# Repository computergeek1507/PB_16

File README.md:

# Copyright and Disclaimer
Copyright: Scott Hanson

This documentation describes Open Hardware and is licensed under the CERN Open Hardware License Version 2 - Strongly Reciprocal. (CERN-OHL-S)

You may redistribute and modify this documentation under the terms of the CERN OHL-S-v2 (https://ohwr.org/cern_ohl_s_v2.txt). This documentation is distributed WITHOUT ANY EXPRESS OR IMPLIED WARRANTY, INCLUDING OF MERCHANTABILITY, SATISFACTORY QUALITY AND FITNESS FOR A PARTICULAR PURPOSE. Please see the CERN OHL v2-S for applicable conditions

**Under CERN OHL-S-v2, derivative work must be publicly released as defined in subsection 3.3**

# BBB/PB 'Family' of Controllers

The PB16/BBB16 Pixel Controllers are designed as open source DIY hobbyist controllers. 
They all run FPP to drives the ports and serial ports. 
They are designed to be modular and support many use cases. It runs a full Linux operating system with ethernet, WIFI and audio supported over the USB port. It can run in standalone, or be used with other controllers/devices. All the design files are open source and available on github. Open source applications were used to create the controllers. [KiCad](http://kicad.org/) was used for the PCB design, and [LibreOffice](https://www.libreoffice.org/) for the documentation.

# [PB 16v1](PB_16v1/README.md)
The "Original" Pocketbeagle Version with 16 pixel ports, 2 serial ports and an expansion header for additional 16 pixel outputs.
The design was made with all through hole components for easy assembly by most users.

# [PB 16v2](PB_16v2_SMD/README.md)
The PB 16v2 is a Surface Mount(SMD) Pocketbeagle Version with 16 pixel ports, 1 remote differential port, 2 serial ports, and an expansion header for additional 16 pixel outputs. The v2 has an improved reverse protect circuit and USB power supply circuit.

# [BBB 16v2](BBB_16/README.md)
The BBB 16v2 is a BeagleBone Version with 16 pixel ports, 1 remote differential port, 2 serial ports, and an expansion header for additional 16 pixel outputs. Uses Falcon v4 (24 pin) Expansion Pinout.

# [BBB 16v2 SMD](BBB_16_SMD/README.md) 
The BBB 16v2 SMD is a Surface Mount(SMD) BeagleBone Version with 16 pixel ports, 1 remote differential port, 2 serial ports, and an expansion header for additional 16 pixel outputs. Uses Falcon v4 (24 pin) Expansion Pinout.

### Common Features of the PB 16v1, PB 16v2, & BBB 16v2
* Powered by FPP Falcon Player
* Standalone/Master/Remote/Bridge Support
* 16 3-Wire Pixel Ports
* 700 pixel per output at 40 FPS or 1300 at 20 FPS
* 2 DMX Serial Outputs
* Fused Powered DMX Output
* USB port for Ethernet,WIFI, or Audio
* OLED Display header
* Adafruit Real Time Clock Header Connector
* 2 pin GPIO Header for Push Button or Relay Support
* 5v - 24v Vin Support
* Expansion Header for additional 16 pixel outputs, Supports Falcon v3 (40 pin) Expansion Boards.

### Features of the PB 16v1
* Through Hole Assemply
* 1 RJ-45 Connector with DMX/Renard Wiring Support.
* 1 RJ-45 Connector with DMX/LOR Wiring Support.
* Only Supports DMX Protocol over Serial Ports.

### Features of the PB 16v2 & BBB 16v2
* 1 RJ-45 Connector for a remote differential port.
* 1 RJ-45 Connector with DMX/LOR Wiring Support.
* Supports DMX/Renard/Lor Protocol over Serial Ports.

## [Ordering Instructions](https://github.com/computergeek1507/PB_16/blob/master/JLC_PCB.md)
## [Flashing EEPROM Instructions](https://github.com/computergeek1507/PB_16/blob/master/Flashing_EEPROM.md)

## Variants
I created different variants of the PB 16, to fit my specific needs.
* [**PB 16v1**](PB_16v1/README.md) - Original Pocketbeagle Version with 16 pixel ports, 2 serial ports and an expansion header(40 pins) for additional 16 pixel outputs.
* [**PB 16v2**](PB_16v2_SMD/README.md) - **Surface Mount(SMD)** Pocketbeagle Version with 16 pixel ports, 1 remote differential port, 2 serial ports, and an expansion header(40 pins) for additional 16 pixel outputs.
* [**BBB 16v2**](BBB_16/README.md) - Beaglebone Version with 16 pixel ports, 1 remote differential port, 2 serial ports and an expansion header for additional 16 pixel outputs. Uses Falcon v4 Expansion Pinout(24 pins).
* [**BBB 16v2 SMD**](BBB_16_SMD/README.md) - **Surface Mount(SMD)** Beaglebone Version with 16 pixel ports, 1 remote differential port, 2 serial ports and an expansion header for additional 16 pixel outputs. Uses Falcon v4 Expansion Pinout(24 pins).
* [**BBB 16 Flex**](BBB_16_Flex/README.md) - BBB 16 PCB to use with the HolidayCoro Flex System. This is a **Surface Mount(SMD)** Design.
* [**BBB 16 Expansion**](BBB_16_Expansion/README.md) - BBB 16v2 PCB with Three Expansion Board Ports for 48 outputs. Uses Falcon v4 Expansion Pinout. This is a **Surface Mount(SMD)** Design.
* [**PB 16 Expansion**](PB_16_Expansion/README.md) - Small Form Factor PB 16 with Two Expansion Board Ports(40 pins) for 32 outputs.
* [**PB 16 Mini**](PB_16_Mini/README.md) - Small Form Factor PB 16 with one Expansion Board Port(40 pins) for 16 ouputs and two Serial Outputs.
* [**PB 16 Flex**](PB_16_Flex/README.md) - PB 16 PCB to use with the HolidayCoro Flex System.
<!--- * [**PB 16 E682**](PB_16_E682/README.md) - Adapter PCB to use a Pocketbeagle with a Sandevice E682. (This is a proof of concept, not designed for extended use)-->
* [**PB 16 E682 Serial**](PB_16_E682_Serial/README.md) - Serial Output PCB to for PB 16 E682 or PB 16 Expansion.

## Addon Boards

The PB16 Controller contains an expansion header. The expansion header can drive 16 additional pixel ports. I have also created addition addon boards to work with the expansion port. These Expansions will work with Kulp Controllers, but **not** Falcon Controllers.

* [**16 Expansion**](16_Expansion/README.md) - 16 Port Local Expansion. Supports PB 16 (40 pins) Connectors.
* [**16 Expansion 24pin**](16_Expansion_24pin/README.md) - 16 Port Local Expansion. Supports BBB 16v2 (24 pins) Connectors.
* [**16 Expansion SMD**](16_Expansion_SMD/README.md) - 16 Port Local Expansion. Supports PB 16 (40 pins) Connectors. This is a **Surface Mount(SMD)** Design.
* [**16 Expansion SMD 24pin**](16_Expansion_SMD_24pin/README.md) - 16 Port Local Expansion. Supports BBB 16v2 (24 pins) Connectors. This is a **Surface Mount(SMD)** Design.
* [**Diff Expansion**](Diff_Expansion/README.md) - 4 Port Remote Differential Expansion. Supports PB 16 (40 pins) & BBB 16 (24 pins) Connectors.
* [**Multi Expansion**](Multi_Expansion/README.md) - 8 Port Local & 2 Port Remote Differential Expansion. **Only Supports PB 16 (40 pins) Connectors.**
* [**Quad Diff Out**](Quad_Diff_Out/README.md) - 1 Port Remote Differential Expansion.
* [**Four Out**](Four_Out/README.md) - 4 Port Local Expansion. Supports PB 16 (40 pins) & BBB 16 (24 pins) Connectors.
* [**Receiver Out**](Receiver_Out/README.md) - 4 Port Remote Receiver Board for use with Remote Differential Expansions.
* [**Receiver Out SMD**](Receiver_Out_SMD/README.md) - 4 Port Remote Receiver Board for use with Remote Differential Expansions. This is a **Surface Mount(SMD)** Design.

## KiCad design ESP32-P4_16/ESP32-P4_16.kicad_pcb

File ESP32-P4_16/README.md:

# Copyright and Disclaimer
Copyright: Scott Hanson

This documentation describes Open Hardware and is licensed under the CERN Open Hardware License Version 2 - Strongly Reciprocal. (CERN-OHL-S)

You may redistribute and modify this documentation under the terms of the CERN OHL-S-v2 (https://ohwr.org/cern_ohl_s_v2.txt). This documentation is distributed WITHOUT ANY EXPRESS OR IMPLIED WARRANTY, INCLUDING OF MERCHANTABILITY, SATISFACTORY QUALITY AND FITNESS FOR A PARTICULAR PURPOSE. Please see the CERN OHL v2-S for applicable conditions

**Under CERN OHL-S-v2, derivative work must be publicly released as defined in subsection 3.3**

# ESP32-P4 16

**WIP, Do not use**

The ESP32-P4 16 is a ESP32-P4 based 16 port controller. All the design files are open source and available on github.

## [Interactive BOM](https://computergeek1507.github.io/PB_16/ESP32-P4_16/bom/ibom)

## [Part BOM](https://github.com/computergeek1507/PB_16/raw/master/ESP32-P4_16/ESP32-P4_16_BOM.ods)

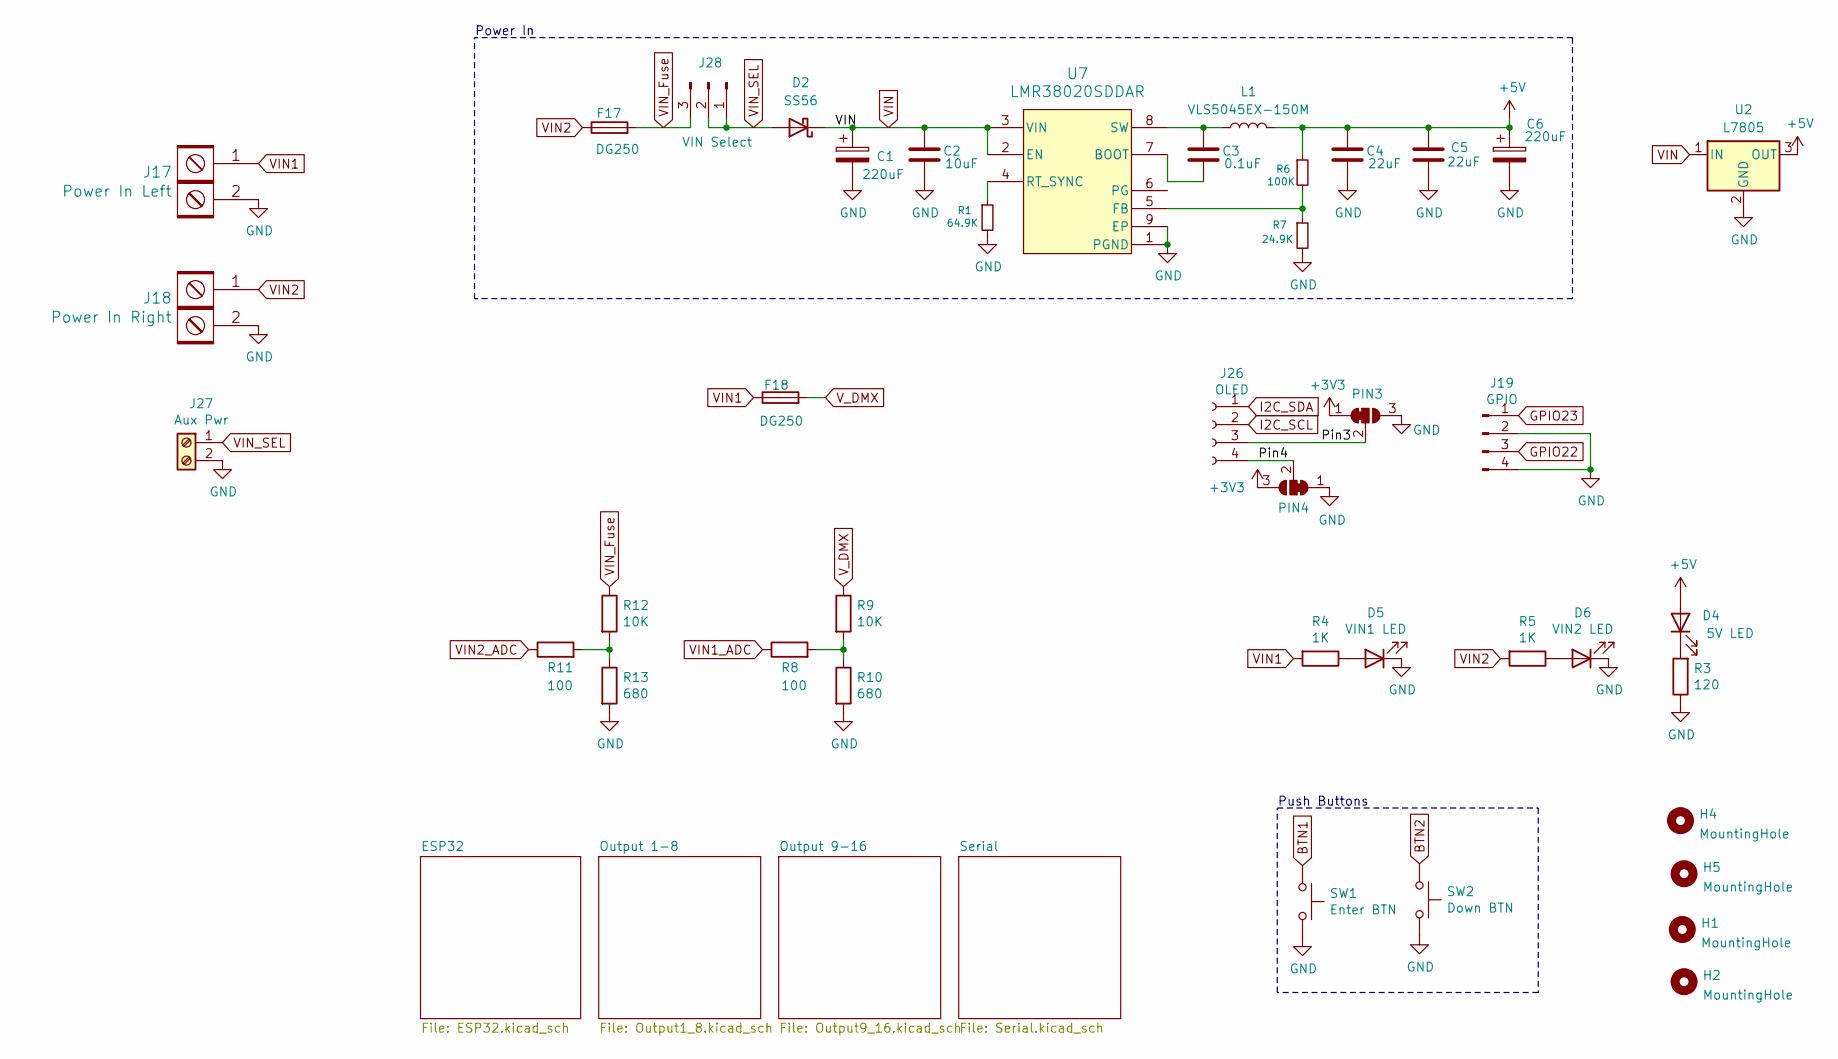
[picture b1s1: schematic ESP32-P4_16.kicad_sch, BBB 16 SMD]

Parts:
C1, C6: 220uF; CP_Elec_8x10.5; LCSC C3340
C2: 10uF; C_1206_3216Metric; LCSC_PN C13585
C3: 0.1uF; C_0603_1608Metric; MPN CC0603KRX7R9BB104; LCSC C14663
C4, C5: 22uF; C_1206_3216Metric; LCSC_PN C1859
D2: SS56; D_SMA; LCSC C65009
D4: 5V LED; LED_0603_1608Metric; MPN LTST-C190KRKT; Digi-Key_PN 160-1436-2-ND
D5: VIN1 LED; LED_0603_1608Metric; MPN LTST-C190KRKT; Digi-Key_PN 160-1436-2-ND
D6: VIN2 LED; LED_0603_1608Metric; MPN LTST-C190KRKT; Digi-Key_PN 160-1436-2-ND
F17: DG250; Fuse_1812_4532Metric; MPN 3544-2
F18: DG250; Fuse_1812_4532Metric
H1, H2, H4, H5: MountingHole; MountingHole_3.7mm
J17: Power In Left; BARRIER_BLOCK_1ROW_2POS_P9.5MM; MPN OSTYK51102030; Digi-Key_PN ED2953-ND
J18: Power In Right; BARRIER_BLOCK_1ROW_2POS_P9.5MM; MPN OSTYK51102030; Digi-Key_PN ED2953-ND
J19: GPIO; JST_XH_B4B-XH-A_1x04_P2.50mm_Vertical; MPN B4B-XH-A(LF)(SN); Digi-Key_PN 455-2249-ND
J26: OLED; OLED-SSD1306-128X64-I2C-THT_2HOLE; MPN PPTC041LFBN-RC; Digi-Key_PN S7002-ND
J27: Aux Pwr; PHOENIX_MKDS1_2-3.81; MPN 1727010; Digi-Key_PN 277-1947-ND
J28: VIN Select; PinHeader_1x03_P2.54mm_Vertical; MPN 61300311121; Digi-Key_PN 732-5316-ND
L1: VLS5045EX-150M; IND_VLS5045EX-150M; MPN VLS5045EX-150M; Digi-Key_PN 445-174845-1-ND
PIN3: Jumper; SolderJumper-3_P1.3mm_Bridged12_Pad1.0x1.5mm
PIN4: JUMPER; SolderJumper-3_P1.3mm_Bridged12_Pad1.0x1.5mm
R1: 64.9K; R_0603_1608Metric; LCSC C14891
R3: 120; R_0603_1608Metric; MPN CRGCQ0603F120R; Digi-Key_PN A129677CT-ND
R4, R5: 1K; R_0603_1608Metric; MPN RC0603FR-071KL; Digi-Key_PN 311-1.00KHRTR-ND
R6: 100K; R_0603_1608Metric; LCSC C25803
R7: 24.9K; R_0603_1608Metric; LCSC C25962
R8, R11: 100; R_0603_1608Metric; MPN RMCF0603FT100R; Digi-Key_PN RMCF0603FT100RCT-ND
R9, R12: 10K; R_0603_1608Metric; MPN RC0603FR-0710KL; Digi-Key_PN 311-10.0KHRCT-ND
R10, R13: 680; R_0603_1608Metric; MPN RC0603FR-07680RL; Digi-Key_PN 311-680HRCT-ND
SW1: Enter BTN; SW_Push_1P1T_NO_6x6mm_H9.5mm; MPN PTS645SL50SMTR92 LFS; Digi-Key_PN CKN9088CT-ND
SW2: Down BTN; SW_Push_1P1T_NO_6x6mm_H9.5mm; MPN PTS645SL50SMTR92 LFS; Digi-Key_PN CKN9088CT-ND
U2: L7805; OKI-78SR_Horz
U7: LMR38020SDDAR; DDA0008E-IPC_A; MPN LMR38020SDDAR; Digi-Key_PN 296-LMR38020SDDARCT-ND

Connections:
+3V3: PIN3.1 (A), PIN4.3 (B); also elsewhere on the board
+5V: C4.1, C5.1, C6.1, D4.2 (A), L1.2, R6.1, U2.3 (OUT); also elsewhere on the board
/Pin3: J26.3, PIN3.2 (C)
/Pin4: J26.4, PIN4.2 (C)
BTN1: SW1.1; also elsewhere on the board
BTN2: SW2.1; also elsewhere on the board
GND: C1.2, C2.2, C4.2, C5.2, C6.2, D5.1 (K), D6.1 (K), J17.2, J18.2, J19.2, J19.4, J27.2, PIN3.3 (B), PIN4.1 (A), R1.2, R3.1, R7.2, R10.2, R13.2, SW1.2, SW2.2, U2.2 (GND), U7.1 (PGND), U7.9 (EP); also elsewhere on the board
GPIO22: J19.3; also elsewhere on the board
GPIO23: J19.1; also elsewhere on the board
I2C_SCL: J26.2; also elsewhere on the board
I2C_SDA: J26.1; also elsewhere on the board
unnamed: D4.1 (K), R3.2
unnamed: D5.2 (A), R4.1
unnamed: D6.2 (A), R5.1
unnamed: R8.2, R9.2, R10.1
unnamed: R11.2, R12.2, R13.1
unnamed: C3.2, U7.7 (BOOT)
unnamed: R6.2, R7.1, U7.5 (FB)
unnamed: R1.1, U7.4 (RT_SYNC)
unnamed: C3.1, L1.1, U7.8 (SW)
VIN: C1.1, C2.1, D2.1 (K), U2.1 (IN), U7.2 (EN), U7.3 (VIN)
VIN1: F18.1, J17.1, R4.2; also elsewhere on the board
VIN1_ADC: R8.1; also elsewhere on the board
VIN2: F17.1, J18.1, R5.2; also elsewhere on the board
VIN2_ADC: R11.1; also elsewhere on the board
VIN_Fuse: F17.2, J28.3, R12.1
VIN_SEL: D2.2 (A), J27.1, J28.1, J28.2
V_DMX: F18.2, R9.1; also elsewhere on the board

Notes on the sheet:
Push Buttons
Power In

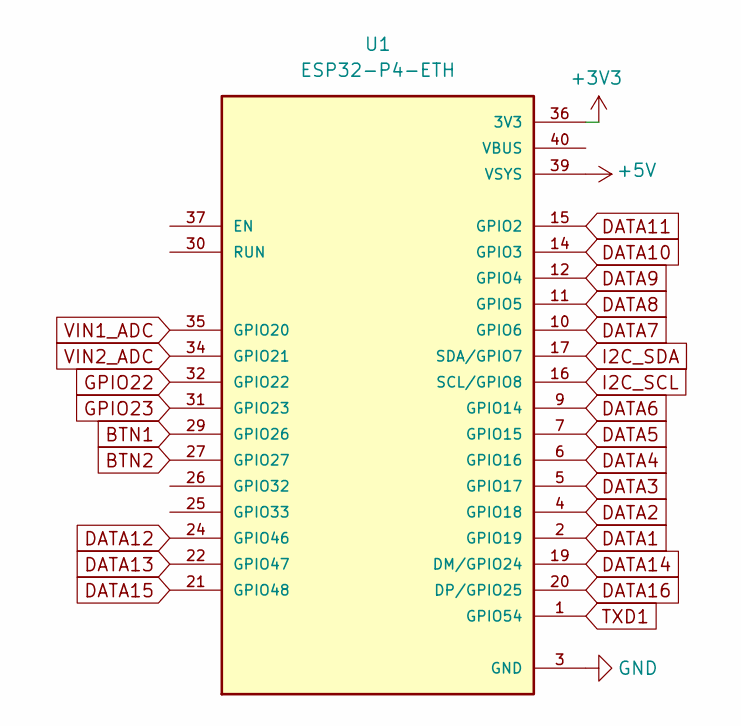
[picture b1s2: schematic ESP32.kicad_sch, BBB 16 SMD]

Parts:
U1: ESP32-P4-ETH; MODULE_ESP32-P4-ETH

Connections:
+3V3: U1.36 (3V3); also elsewhere on the board
+5V: U1.39 (VSYS); also elsewhere on the board
BTN1: U1.29 (GPIO26); also elsewhere on the board
BTN2: U1.27 (GPIO27); also elsewhere on the board
DATA1: U1.2 (GPIO19); also elsewhere on the board
DATA2: U1.4 (GPIO18); also elsewhere on the board
DATA3: U1.5 (GPIO17); also elsewhere on the board
DATA4: U1.6 (GPIO16); also elsewhere on the board
DATA5: U1.7 (GPIO15); also elsewhere on the board
DATA6: U1.9 (GPIO14); also elsewhere on the board
DATA7: U1.10 (GPIO6); also elsewhere on the board
DATA8: U1.11 (GPIO5); also elsewhere on the board
DATA9: U1.12 (GPIO4); also elsewhere on the board
DATA10: U1.14 (GPIO3); also elsewhere on the board
DATA11: U1.15 (GPIO2); also elsewhere on the board
DATA12: U1.24 (GPIO46); also elsewhere on the board
DATA13: U1.22 (GPIO47); also elsewhere on the board
DATA14: U1.19 (DM/GPIO24); also elsewhere on the board
DATA15: U1.21 (GPIO48); also elsewhere on the board
DATA16: U1.20 (DP/GPIO25); also elsewhere on the board
GND: U1.3 (GND), U1.8 (GND), U1.13 (GND), U1.18 (GND), U1.23 (GND), U1.28 (GND), U1.33 (GND), U1.38 (GND); also elsewhere on the board
GPIO22: U1.32 (GPIO22); also elsewhere on the board
GPIO23: U1.31 (GPIO23); also elsewhere on the board
I2C_SCL: U1.16 (SCL/GPIO8); also elsewhere on the board
I2C_SDA: U1.17 (SDA/GPIO7); also elsewhere on the board
TXD1: U1.1 (GPIO54); also elsewhere on the board
VIN1_ADC: U1.35 (GPIO20); also elsewhere on the board
VIN2_ADC: U1.34 (GPIO21); also elsewhere on the board

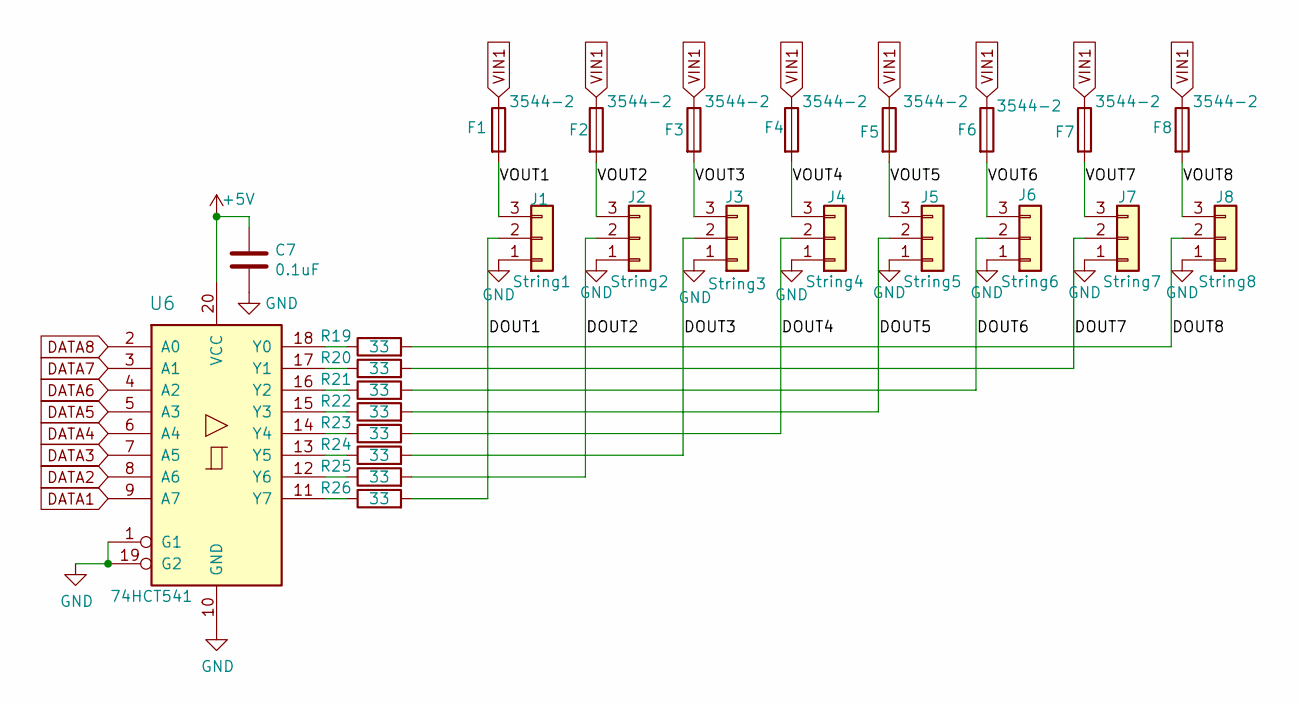
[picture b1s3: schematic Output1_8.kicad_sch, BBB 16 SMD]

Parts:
C7: 0.1uF; C_0603_1608Metric; MPN CL10B104KB8NNWC; Digi-Key_PN 1276-1935-2-ND
F1, F2, F3, F4, F5, F6, F7, F8: 3544-2; Fuse_1812_4532Metric; MPN 3544-2
J1: String1; DG250-3.5-03P; MPN 1843619/OSTTJ0311530
J2: String2; DG250-3.5-03P; MPN 1843619/OSTTJ0311530
J3: String3; DG250-3.5-03P; MPN 1843619/OSTTJ0311530
J4: String4; DG250-3.5-03P; MPN 1843619/OSTTJ0311530
J5: String5; DG250-3.5-03P; MPN 1843619/OSTTJ0311530
J6: String6; DG250-3.5-03P; MPN 1843619/OSTTJ0311530
J7: String7; DG250-3.5-03P; MPN 1843619/OSTTJ0311530
J8: String8; DG250-3.5-03P; MPN 1843619/OSTTJ0311530
R19, R20, R21, R22, R23, R24, R25, R26: 33; R_0603_1608Metric; MPN CN34J330CT; LCSC C23140
U6: 74HCT541; TSSOP-20_4.4x6.5mm_P0.65mm; MPN SN74HCT541PWR; Digi-Key_PN MC74HCT541ADTR2GOSTR-ND

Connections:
+5V: C7.1, U6.20 (VCC); also elsewhere on the board
/Output 1-8/DOUT1: J1.2, R26.2
/Output 1-8/DOUT2: J2.2, R25.2
/Output 1-8/DOUT3: J3.2, R24.2
/Output 1-8/DOUT4: J4.2, R23.2
/Output 1-8/DOUT5: J5.2, R22.2
/Output 1-8/DOUT6: J6.2, R21.2
/Output 1-8/DOUT7: J7.2, R20.2
/Output 1-8/DOUT8: J8.2, R19.2
/Output 1-8/VOUT1: F1.2, J1.3
/Output 1-8/VOUT2: F2.2, J2.3
/Output 1-8/VOUT3: F3.2, J3.3
/Output 1-8/VOUT4: F4.2, J4.3
/Output 1-8/VOUT5: F5.2, J5.3
/Output 1-8/VOUT6: F6.2, J6.3
/Output 1-8/VOUT7: F7.2, J7.3
/Output 1-8/VOUT8: F8.2, J8.3
DATA1: U6.9 (A7); also elsewhere on the board
DATA2: U6.8 (A6); also elsewhere on the board
DATA3: U6.7 (A5); also elsewhere on the board
DATA4: U6.6 (A4); also elsewhere on the board
DATA5: U6.5 (A3); also elsewhere on the board
DATA6: U6.4 (A2); also elsewhere on the board
DATA7: U6.3 (A1); also elsewhere on the board
DATA8: U6.2 (A0); also elsewhere on the board
GND: C7.2, J1.1, J2.1, J3.1, J4.1, J5.1, J6.1, J7.1, J8.1, U6.1 (G1), U6.10 (GND), U6.19 (G2); also elsewhere on the board
unnamed: R19.1, U6.18 (Y0)
unnamed: R20.1, U6.17 (Y1)
unnamed: R21.1, U6.16 (Y2)
unnamed: R22.1, U6.15 (Y3)
unnamed: R23.1, U6.14 (Y4)
unnamed: R24.1, U6.13 (Y5)
unnamed: R25.1, U6.12 (Y6)
unnamed: R26.1, U6.11 (Y7)
VIN1: F1.1, F2.1, F3.1, F4.1, F5.1, F6.1, F7.1, F8.1; also elsewhere on the board

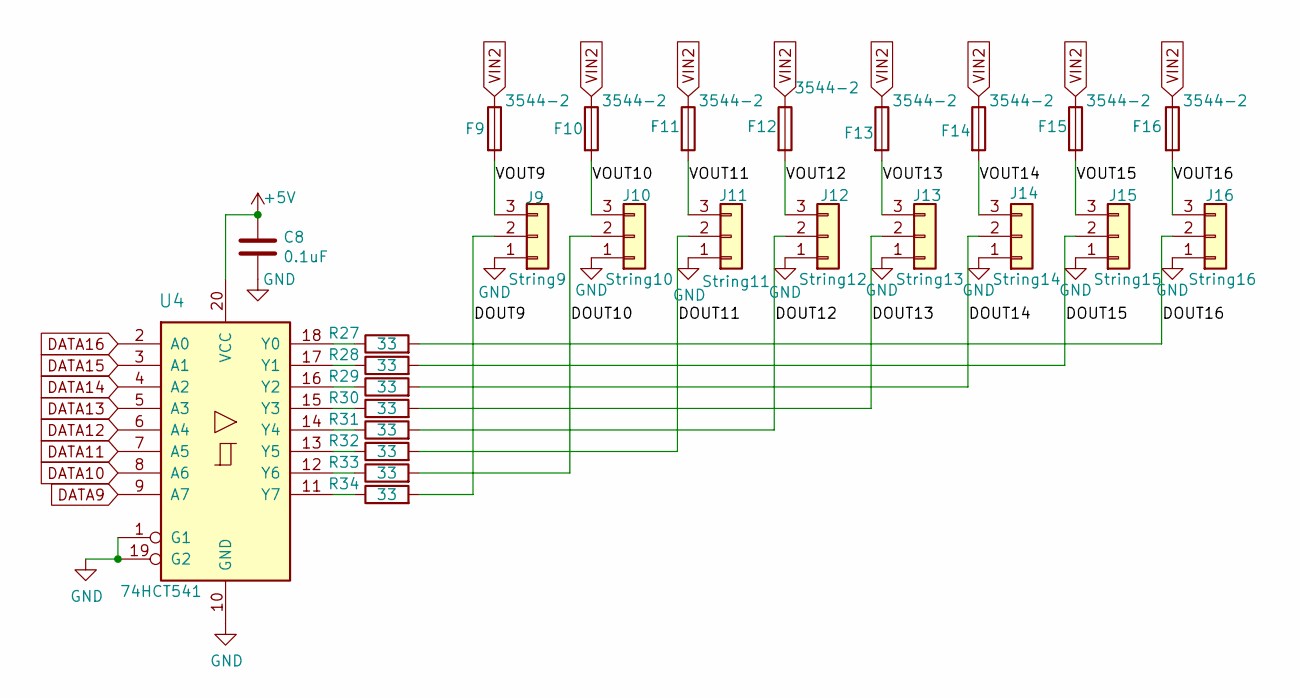
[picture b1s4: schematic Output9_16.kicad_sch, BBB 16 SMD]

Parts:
C8: 0.1uF; C_0603_1608Metric; MPN CL10B104KB8NNWC; Digi-Key_PN 1276-1935-2-ND
F9, F10, F11, F12, F13, F14, F15, F16: 3544-2; Fuse_1812_4532Metric; MPN 3544-2
J9: String9; DG250-3.5-03P; MPN 1843619/OSTTJ0311530
J10: String10; DG250-3.5-03P; MPN 1843619/OSTTJ0311530
J11: String11; DG250-3.5-03P; MPN 1843619/OSTTJ0311530
J12: String12; DG250-3.5-03P; MPN 1843619/OSTTJ0311530
J13: String13; DG250-3.5-03P; MPN 1843619/OSTTJ0311530
J14: String14; DG250-3.5-03P; MPN 1843619/OSTTJ0311530
J15: String15; DG250-3.5-03P; MPN 1843619/OSTTJ0311530
J16: String16; DG250-3.5-03P; MPN 1843619/OSTTJ0311530
R27, R28, R29, R30, R31, R32, R33, R34: 33; R_0603_1608Metric; MPN CN34J330CT; LCSC C23140
U4: 74HCT541; TSSOP-20_4.4x6.5mm_P0.65mm; MPN SN74HCT541PWR; Digi-Key_PN MC74HCT541ADTR2GOSTR-ND

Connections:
+5V: C8.1, U4.20 (VCC); also elsewhere on the board
/Output 9-16/DOUT9: J9.2, R34.2
/Output 9-16/DOUT10: J10.2, R33.2
/Output 9-16/DOUT11: J11.2, R32.2
/Output 9-16/DOUT12: J12.2, R31.2
/Output 9-16/DOUT13: J13.2, R30.2
/Output 9-16/DOUT14: J14.2, R29.2
/Output 9-16/DOUT15: J15.2, R28.2
/Output 9-16/DOUT16: J16.2, R27.2
/Output 9-16/VOUT9: F9.2, J9.3
/Output 9-16/VOUT10: F10.2, J10.3
/Output 9-16/VOUT11: F11.2, J11.3
/Output 9-16/VOUT12: F12.2, J12.3
/Output 9-16/VOUT13: F13.2, J13.3
/Output 9-16/VOUT14: F14.2, J14.3
/Output 9-16/VOUT15: F15.2, J15.3
/Output 9-16/VOUT16: F16.2, J16.3
DATA9: U4.9 (A7); also elsewhere on the board
DATA10: U4.8 (A6); also elsewhere on the board
DATA11: U4.7 (A5); also elsewhere on the board
DATA12: U4.6 (A4); also elsewhere on the board
DATA13: U4.5 (A3); also elsewhere on the board
DATA14: U4.4 (A2); also elsewhere on the board
DATA15: U4.3 (A1); also elsewhere on the board
DATA16: U4.2 (A0); also elsewhere on the board
GND: C8.2, J9.1, J10.1, J11.1, J12.1, J13.1, J14.1, J15.1, J16.1, U4.1 (G1), U4.10 (GND), U4.19 (G2); also elsewhere on the board
unnamed: R27.1, U4.18 (Y0)
unnamed: R28.1, U4.17 (Y1)
unnamed: R29.1, U4.16 (Y2)
unnamed: R30.1, U4.15 (Y3)
unnamed: R31.1, U4.14 (Y4)
unnamed: R32.1, U4.13 (Y5)
unnamed: R33.1, U4.12 (Y6)
unnamed: R34.1, U4.11 (Y7)
VIN2: F9.1, F10.1, F11.1, F12.1, F13.1, F14.1, F15.1, F16.1; also elsewhere on the board

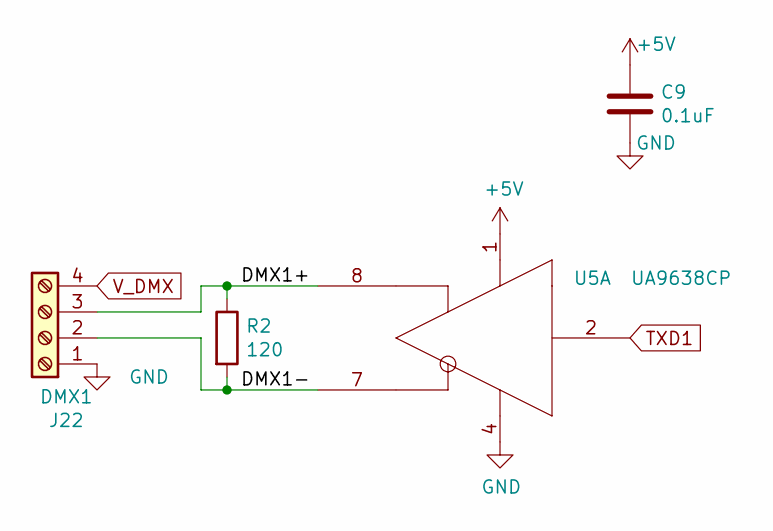
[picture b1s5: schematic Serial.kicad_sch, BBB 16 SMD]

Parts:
C9: 0.1uF; C_0603_1608Metric; MPN CL10B104KB8NNWC; Digi-Key_PN 1276-1935-2-ND
J22: DMX1; TerminalBlock_Phoenix_MKDS-1,5-4_1x04_P5.00mm_Horizontal; MPN 1729034; Digi-Key_PN 277-1238-ND
R2: 120; R_0603_1608Metric; MPN CRGCQ0603F120R; Digi-Key_PN A129677CT-ND
U5: UA9638CP; SOIC-8_3.9x4.9mm_P1.27mm; MPN UA9638CDR; Digi-Key_PN UA9638CP

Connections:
+5V: C9.1, U5.1 (VCC); also elsewhere on the board
/Serial/DMX1+: J22.3, R2.1, U5.8 (OUTB)
/Serial/DMX1-: J22.2, R2.2, U5.7 (OUTA)
GND: C9.2, J22.1, U5.4 (GND); also elsewhere on the board
TXD1: U5.2 (IN); also elsewhere on the board
V_DMX: J22.4; also elsewhere on the board

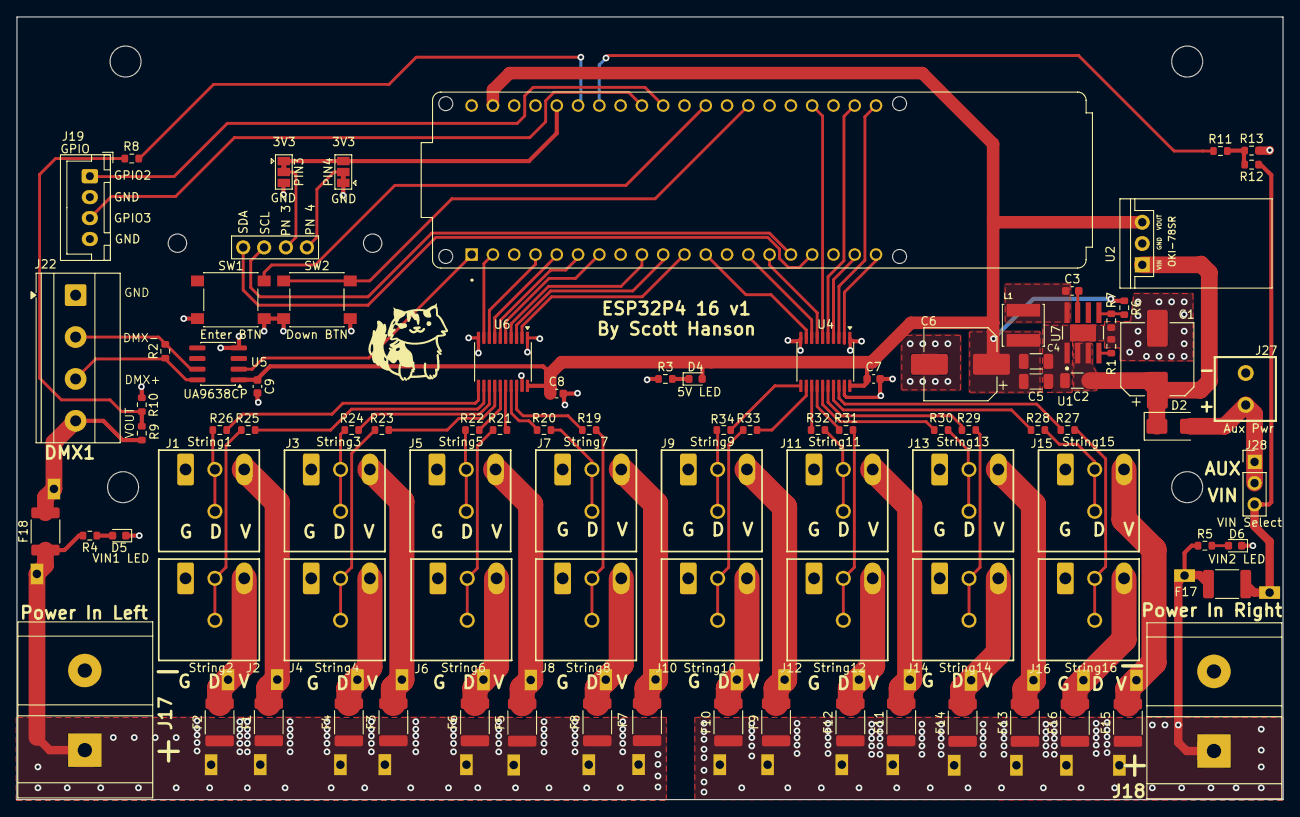
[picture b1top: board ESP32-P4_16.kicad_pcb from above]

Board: 2 copper layers, 151.1 x 93.4 mm, 98 parts (0 on the bottom side), 95 nets.

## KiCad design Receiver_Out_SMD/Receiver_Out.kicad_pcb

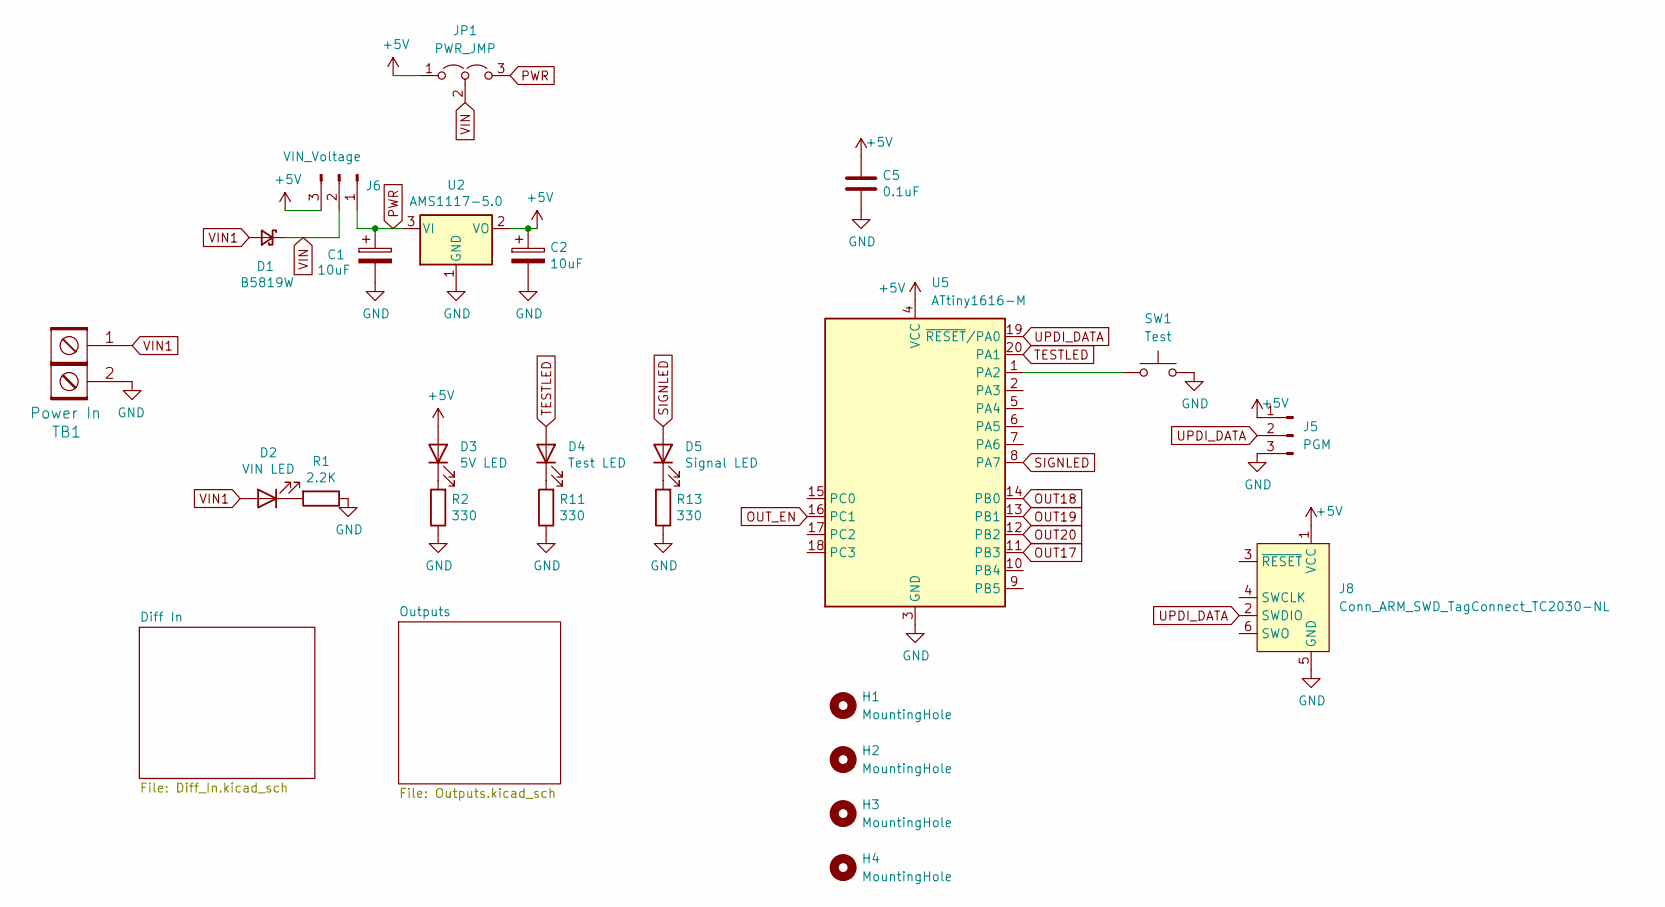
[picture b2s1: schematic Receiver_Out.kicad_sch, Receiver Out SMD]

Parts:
C1, C2: 10uF; C_0805_2012Metric; MPN GRM21BR61E106KA73L; Digi-Key_PN 490-5523-1-ND
C5: 0.1uF; C_0402_1005Metric; MPN 0402B104K160CT; Digi-Key_PN 1292-1630-1-ND
D1: B5819W; D_SOD-123; MPN B5819W-TP; LCSC_PN C8598
D2: VIN LED; LED_0603_1608Metric; MPN 150080RS75000; Digi-Key_PN 732-4984-1-ND
D3: 5V LED; LED_0603_1608Metric; MPN 150080RS75000; Digi-Key_PN 732-4984-1-ND
D4: Test LED; LED_0603_1608Metric; MPN 150080RS75000; Digi-Key_PN 732-4984-1-ND
D5: Signal LED; LED_0603_1608Metric; MPN 150080RS75000; Digi-Key_PN 732-4984-1-ND
H1, H2, H3, H4: MountingHole; MountingHole_3.7mm
J5: PGM; PinHeader_1x03_P2.54mm_Vertical
J6: VIN_Voltage; PinHeader_1x03_P2.54mm_Vertical; MPN 61300311121; Digi-Key_PN 732-5316-ND
J8: Conn_ARM_SWD_TagConnect_TC2030-NL; Tag-Connect_TC2030-IDC-NL_2x03_P1.27mm_Vertical
JP1: PWR_JMP; SolderJumper-3_P2.0mm_Open_TrianglePad1.0x1.5mm
R1: 2.2K; R_0603_1608Metric
R2, R11, R13: 330; R_0603_1608Metric; MPN CRGCQ0603F330R
SW1: Test; SW_Push_1P1T_NO_6x6mm_H9.5mm; MPN 222AMVBAR; LCSC C255812
TB1: Power In; BARRIER_BLOCK_1ROW_2POS; MPN 4DB-P108-02; Digi-Key_PN A98472-ND
U2: AMS1117-5.0; SOT-223-3_TabPin2; MPN LM1117MPX-50NOPB; LCSC_PN C6187
U5: ATtiny1616-M; VQFN-20-1EP_3x3mm_P0.4mm_EP1.7x1.7mm; MPN ATTINY1616-MNR; Digi-Key_PN ATTINY1616-MNRCT-ND

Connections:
+5V: C2.1, C5.1, D3.2 (A), J5.1, J6.3, J8.1 (VCC), JP1.1 (A), U2.2 (VO), U5.4 (VCC); also elsewhere on the board
GND: C1.2, C2.2, C5.2, J5.3, J8.5 (GND), R1.1, R2.1, R11.1, R13.1, SW1.2, TB1.2, U2.1 (GND), U5.3 (GND), U5.21 (GND); also elsewhere on the board
unnamed: D2.1 (K), R1.2
unnamed: D3.1 (K), R2.2
unnamed: D4.1 (K), R11.2
unnamed: D5.1 (K), R13.2
unnamed: SW1.1, U5.1 (PA2)
OUT17: U5.11 (PB3); also elsewhere on the board
OUT18: U5.14 (PB0); also elsewhere on the board
OUT19: U5.13 (PB1); also elsewhere on the board
OUT20: U5.12 (PB2); also elsewhere on the board
OUT_EN: U5.16 (PC1); also elsewhere on the board
PWR: C1.1, J6.1, JP1.3 (B), U2.3 (VI)
SIGNLED: D5.2 (A), U5.8 (PA7)
TESTLED: D4.2 (A), U5.20 (PA1)
UPDI_DATA: J5.2, J8.2 (SWDIO), U5.19 (~RESET/PA0)
VIN: D1.1 (K), J6.2, JP1.2 (C)
VIN1: D1.2 (A), D2.2 (A), TB1.1; also elsewhere on the board

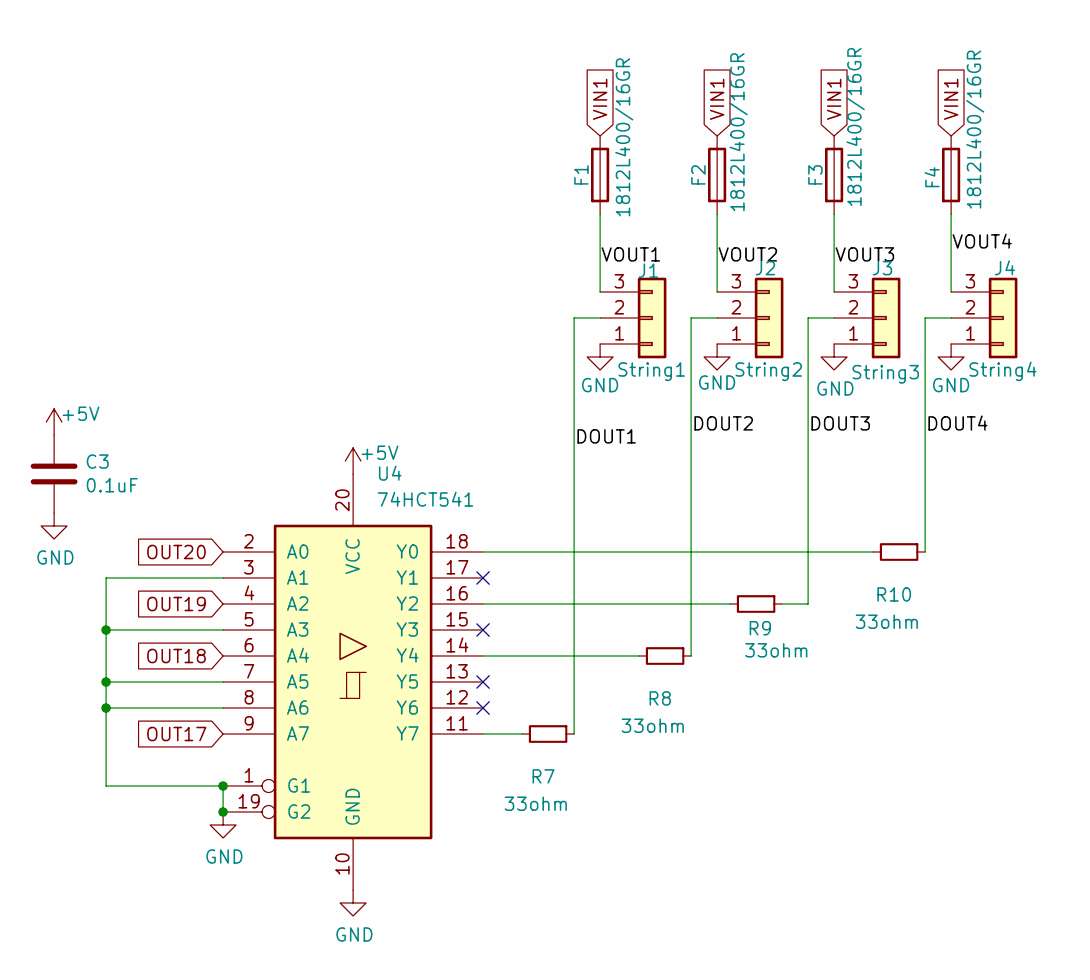
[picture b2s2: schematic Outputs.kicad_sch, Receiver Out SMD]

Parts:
C3: 0.1uF; C_0402_1005Metric; MPN 0402B104K160CT; Digi-Key_PN 1292-1630-1-ND
F1, F2, F3, F4: 1812L400/16GR; Fuse_1812_4532Metric; MPN 3544-2; Digi-Key_PN 36-3544-2-ND
J1: String1; DG250-3.5-03P; MPN 1843619/OSTTJ0311530; Digi-Key_PN 277-5737-ND/ED10555-ND
J2: String2; DG250-3.5-03P; MPN 1843619/OSTTJ0311530; Digi-Key_PN 277-5737-ND/ED10555-ND
J3: String3; DG250-3.5-03P; MPN 1843619/OSTTJ0311530; Digi-Key_PN 277-5737-ND/ED10555-ND
J4: String4; DG250-3.5-03P; MPN 1843619/OSTTJ0311530; Digi-Key_PN 277-5737-ND/ED10555-ND
R7, R8, R9, R10: 33ohm; R_0603_1608Metric; MPN RC0603JR-0733RL; LCSC_PN C23140
U4: 74HCT541; TSSOP-20_4.4x6.5mm_P0.65mm; MPN 74HCT541PW,118; LCSC C436096

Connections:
+5V: C3.1, U4.20 (VCC); also elsewhere on the board
/Outputs/DOUT1: J1.2, R7.1
/Outputs/DOUT2: J2.2, R8.1
/Outputs/DOUT3: J3.2, R9.1
/Outputs/DOUT4: J4.2, R10.1
/Outputs/VOUT1: F1.2, J1.3
/Outputs/VOUT2: F2.2, J2.3
/Outputs/VOUT3: F3.2, J3.3
/Outputs/VOUT4: F4.2, J4.3
GND: C3.2, J1.1, J2.1, J3.1, J4.1, U4.1 (G1), U4.3 (A1), U4.5 (A3), U4.7 (A5), U4.8 (A6), U4.10 (GND), U4.19 (G2); also elsewhere on the board
unnamed: R10.2, U4.18 (Y0)
unnamed: R9.2, U4.16 (Y2)
unnamed: R8.2, U4.14 (Y4)
unnamed: R7.2, U4.11 (Y7)
OUT17: U4.9 (A7); also elsewhere on the board
OUT18: U4.6 (A4); also elsewhere on the board
OUT19: U4.4 (A2); also elsewhere on the board
OUT20: U4.2 (A0); also elsewhere on the board
VIN1: F1.1, F2.1, F3.1, F4.1; also elsewhere on the board

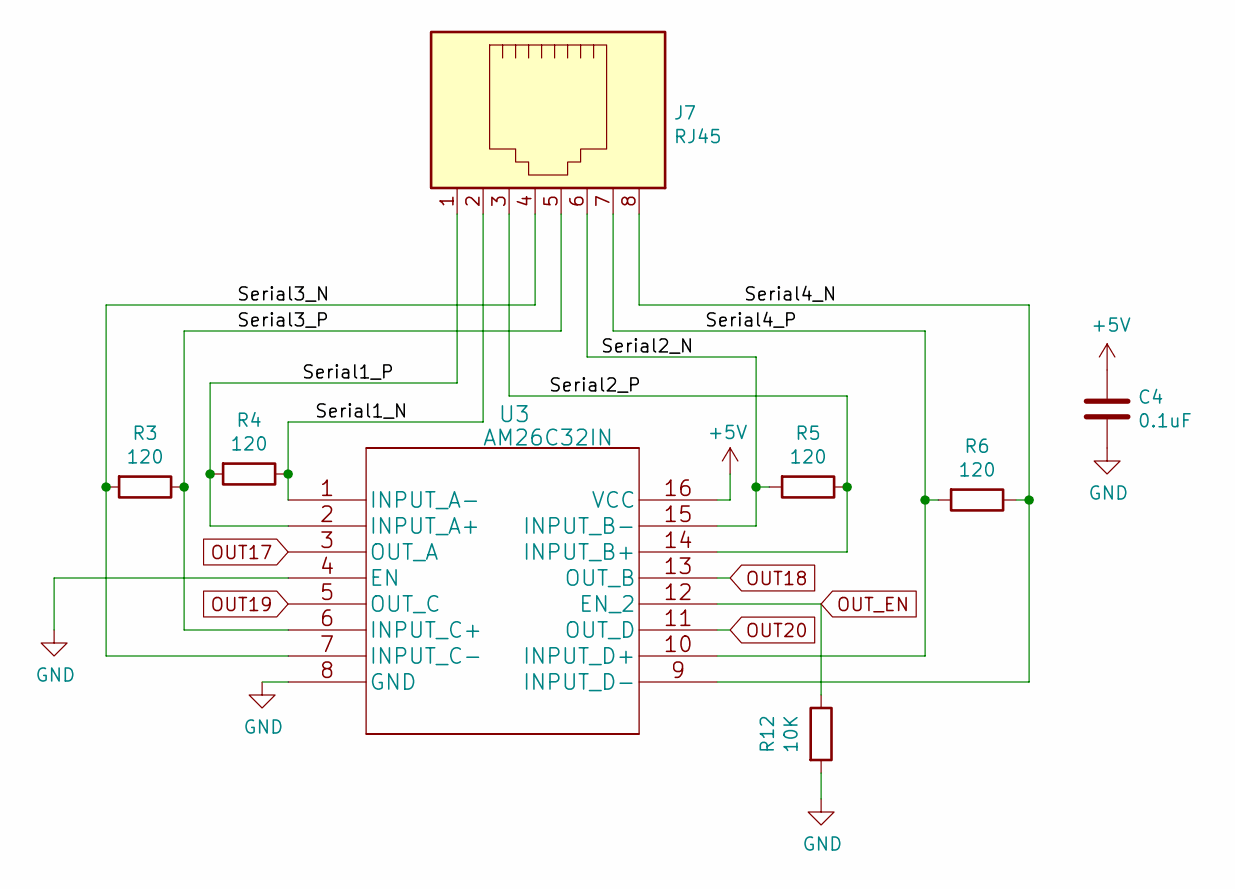
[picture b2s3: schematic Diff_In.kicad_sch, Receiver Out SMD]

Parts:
C4: 0.1uF; C_0402_1005Metric; MPN 0402B104K160CT; Digi-Key_PN 1292-1630-1-ND
J7: RJ45; RJ45_Amphenol_54602-x08_Horizontal; MPN A-2014-2-4-R; Digi-Key_PN AE10392-ND
R3, R4, R5, R6: 120; R_0603_1608Metric; MPN CRGCQ0603F120R; LCSC_PN C22787
R12: 10K; R_0603_1608Metric; MPN RC0603FR-0710KL; LCSC_PN C25804
U3: AM26C32IN; SOIC-16_3.9x9.9mm_P1.27mm; MPN AM26C32INSR; Digi-Key_PN 296-37322-1-ND

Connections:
+5V: C4.1, U3.16 (VCC); also elsewhere on the board
/Diff In/Serial1_N: J7.2, R4.1, U3.1 (INPUT_A-)
/Diff In/Serial1_P: J7.1, R4.2, U3.2 (INPUT_A+)
/Diff In/Serial2_N: J7.6, R5.2, U3.15 (INPUT_B-)
/Diff In/Serial2_P: J7.3, R5.1, U3.14 (INPUT_B+)
/Diff In/Serial3_N: J7.4, R3.2, U3.7 (INPUT_C-)
/Diff In/Serial3_P: J7.5, R3.1, U3.6 (INPUT_C+)
/Diff In/Serial4_N: J7.8, R6.1, U3.9 (INPUT_D-)
/Diff In/Serial4_P: J7.7, R6.2, U3.10 (INPUT_D+)
GND: C4.2, R12.2, U3.4 (EN), U3.8 (GND); also elsewhere on the board
OUT17: U3.3 (OUT_A); also elsewhere on the board
OUT18: U3.13 (OUT_B); also elsewhere on the board
OUT19: U3.5 (OUT_C); also elsewhere on the board
OUT20: U3.11 (OUT_D); also elsewhere on the board
OUT_EN: R12.1, U3.12 (EN_2); also elsewhere on the board

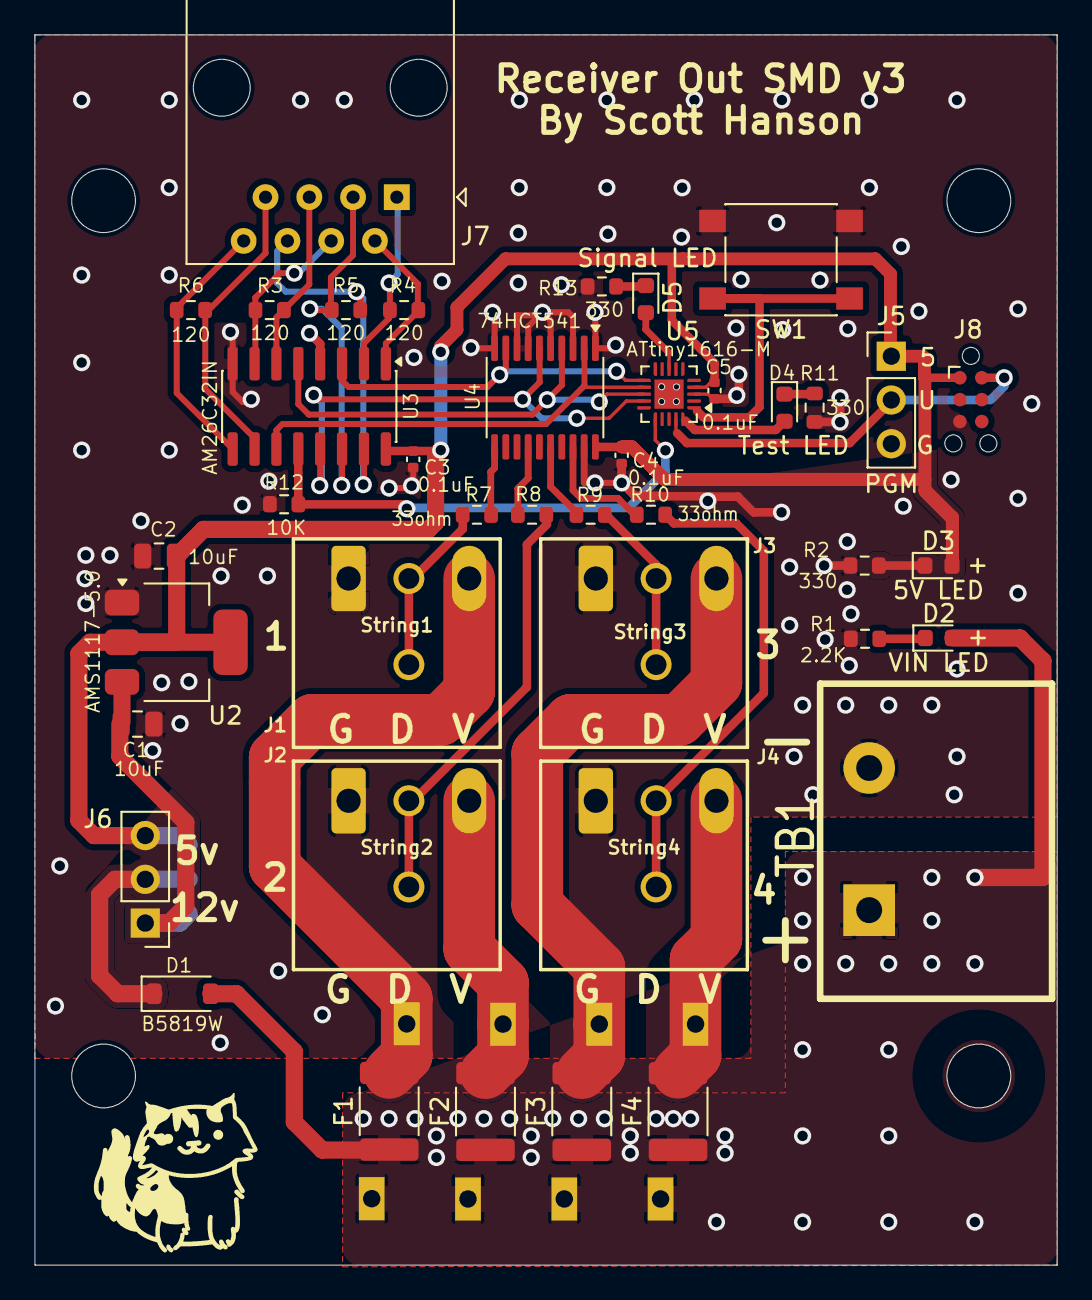
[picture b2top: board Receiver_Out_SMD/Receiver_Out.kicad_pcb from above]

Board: 2 copper layers, 59.3 x 71.4 mm, 46 parts (1 on the bottom side), 38 nets.

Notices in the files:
parts and their libraries:
Copyright 2016 Accelerated Designs. All rights reserved.
